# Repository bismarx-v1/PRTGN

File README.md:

# PRTGN
OwO whats this (This repo contains electronics, mechanical and software data for a protogen visor)

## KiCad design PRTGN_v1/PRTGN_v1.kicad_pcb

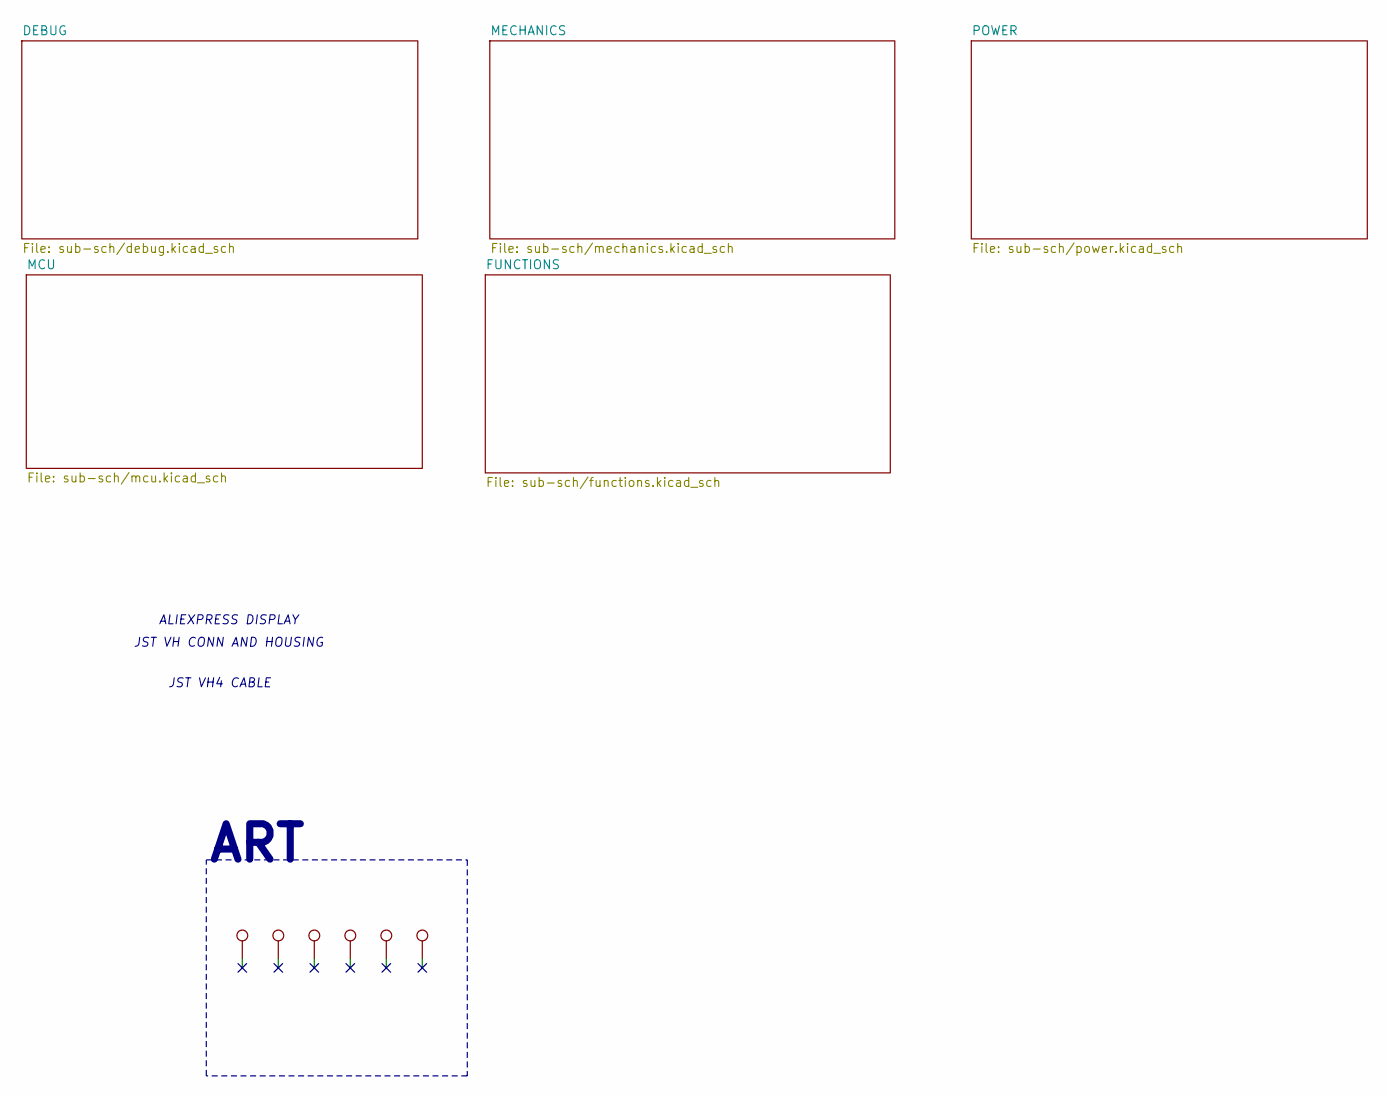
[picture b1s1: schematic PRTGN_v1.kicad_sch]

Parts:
TPd1: TestPoint; APERTURE_ART
TPd2: TestPoint; LEGOSHI_SILK
TPd3: TestPoint; BOYKISSER_IMG
TPd4, TPd6: TestPoint; OWO_IMG
TPd8: TestPoint; PURO_CHANGED_IMG

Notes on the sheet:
JST VH4 CABLE
ALIEXPRESS DISPLAY
ART
JST VH CONN AND HOUSING

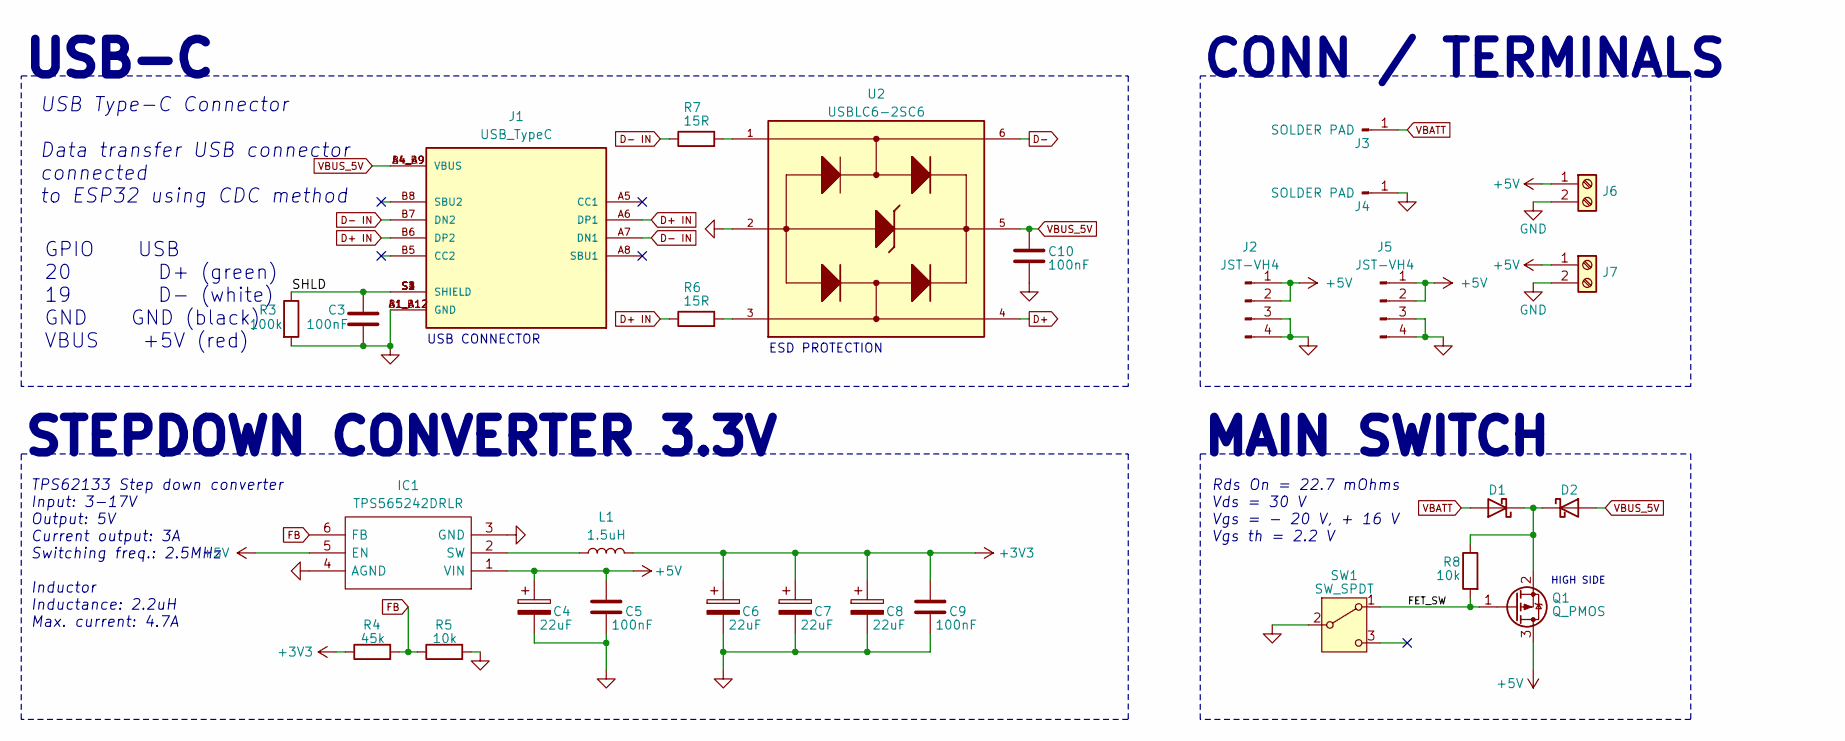
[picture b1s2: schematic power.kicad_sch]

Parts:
C3, C10: 100nF; C_0805_2012Metric
C4, C6, C7, C8: 22uF; CP_EIA-2012-12_Kemet-R
C5, C9: 100nF; C_0805_2012Metric; LCSC C49678
D1, D2: D_Schottky; D_2114_3652Metric
IC1: TPS565242DRLR; SOT-563; Manufacturer_Part_Number TPS565242DRLR; Mouser Part Number 595-TPS565242DRLR
J1: USB_TypeC; HRO_TYPE-C-31-M-12; PARTREV 2020.12.08
J2, J5: JST-VH4; JST_VH_B4P-VH-B_1x04_P3.96mm_Vertical
J3, J4: SOLDER PAD; SolderWirePad_1x01_SMD
J6, J7: Screw_Terminal_01x02; TerminalBlock_Phoenix_MKDS-1,5-2-5.08_1x02_P5.08mm_Horizont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
L1: 1.5uH; L_Vishay_IHLP-1212
Q1: Q_PMOS; SOT-23-3
R3: 100k; R_0805_2012Metric
R4: 45k; R_0805_2012Metric; LCSC C17470
R5: 10k; R_0805_2012Metric; LCSC C17633
R6, R7: 15R; R_0805_2012Metric
R8: 10k; R_0805_2012Metric
SW1: SW_SPDT; Custom_SPDT_2.5_Switch
U2: USBLC6-2SC6; TSOT-23-6

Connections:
+3V3: C6.1, C7.1, C8.1, C9.1, L1.2, R4.1; also elsewhere on the board
+5V: C4.1, C5.1, IC1.1 (VIN), IC1.5 (EN), J2.1, J2.2, J5.1, J5.2, J6.1, J7.1, Q1.3 (D); also elsewhere on the board
/POWER/FET_SW: Q1.1 (G), R8.2, SW1.1 (A)
/POWER/SHLD: C3.2, J1.S1 (SHIELD), J1.S2 (SHIELD), J1.S3 (SHIELD), J1.S4 (SHIELD), R3.1
D+: U2.4; also elsewhere on the board
D+ IN: J1.A6 (DP1), J1.B6 (DP2), R6.1
D-: U2.6; also elsewhere on the board
D- IN: J1.A7 (DN1), J1.B7 (DN2), R7.1
FB: IC1.6 (FB), R4.2, R5.1
GND: C3.1, C4.2, C5.2, C6.2, C7.2, C8.2, C9.2, C10.2, IC1.3 (GND), IC1.4 (AGND), J1.A1_B12 (GND), J1.B1_A12 (GND), J2.3, J2.4, J4.1, J5.3, J5.4, J6.2, J7.2, R3.2, R5.2, SW1.2 (B), U2.2; also elsewhere on the board
unnamed: D1.1 (K), D2.1 (K), Q1.2 (S), R8.1
unnamed: IC1.2 (SW), L1.1
unnamed: R6.2, U2.3
unnamed: R7.2, U2.1
VBATT: D1.2 (A), J3.1; also elsewhere on the board
VBUS_5V: C10.1, D2.2 (A), J1.A4_B9 (VBUS), J1.B4_A9 (VBUS), U2.5; also elsewhere on the board

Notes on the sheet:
Rds On = 22.7 mOhms Vds = 30 V Vgs = - 20 V, + 16 V Vgs th = 2.2 V
USB CONNECTOR
USB-C
USB Type-C Connector Data transfer USB connector connected to ESP32 using CDC method
ESD PROTECTION
MAIN SWITCH
TPS62133 Step down converter Input: 3-17V Output: 5V Current output: 3A Switching freq.: 2.5MHz Inductor Inductance: 2.2uH Max. current: 4.7A
HIGH SIDE
GPIO USB 20 D+ (green) 19 D- (white) GND GND (black) VBUS +5V (red)
STEPDOWN CONVERTER 3.3V
CONN / TERMINALS

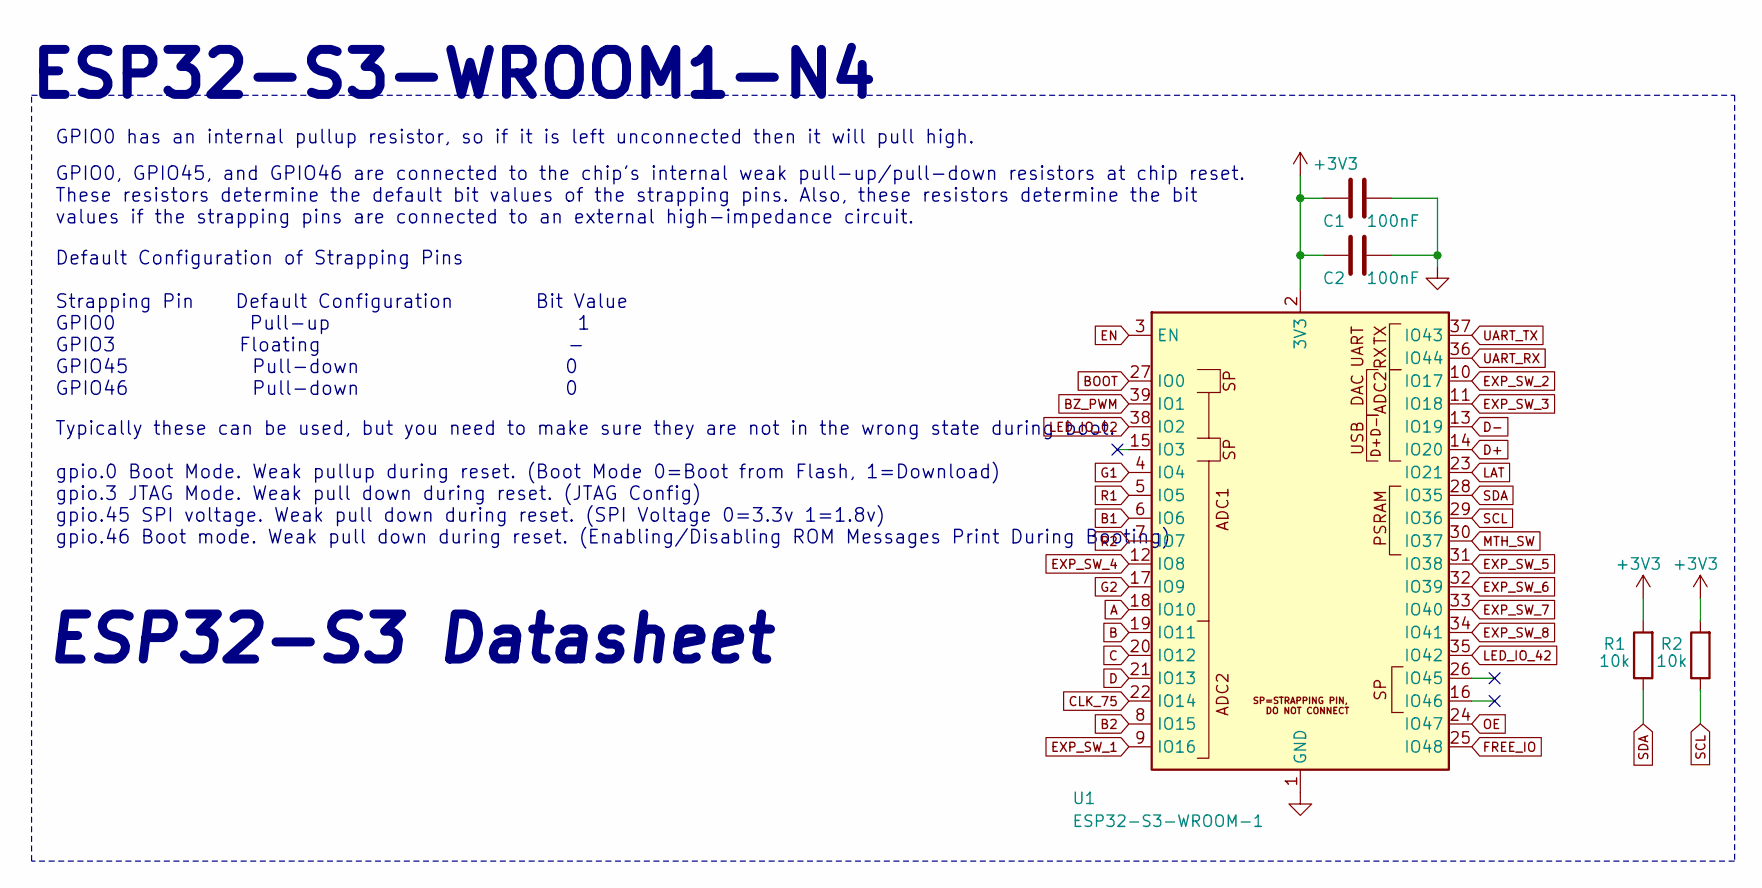
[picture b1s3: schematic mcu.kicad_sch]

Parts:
C1, C2: 100nF; C_0805_2012Metric
R1, R2: 10k; R_0805_2012Metric
U1: ESP32-S3-WROOM-1

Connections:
+3V3: C1.1, C2.1, R1.2, R2.2, U1.2 (3V3); also elsewhere on the board
A: U1.18 (IO10); also elsewhere on the board
B: U1.19 (IO11); also elsewhere on the board
B1: U1.6 (IO6); also elsewhere on the board
B2: U1.8 (IO15); also elsewhere on the board
BOOT: U1.27 (IO0); also elsewhere on the board
BZ_PWM: U1.39 (IO1); also elsewhere on the board
C: U1.20 (IO12); also elsewhere on the board
CLK_75: U1.22 (IO14); also elsewhere on the board
D: U1.21 (IO13); also elsewhere on the board
D+: U1.14 (IO20); also elsewhere on the board
D-: U1.13 (IO19); also elsewhere on the board
EN: U1.3 (EN); also elsewhere on the board
EXP_SW_1: U1.9 (IO16); also elsewhere on the board
EXP_SW_2: U1.10 (IO17); also elsewhere on the board
EXP_SW_3: U1.11 (IO18); also elsewhere on the board
EXP_SW_4: U1.12 (IO8); also elsewhere on the board
EXP_SW_5: U1.31 (IO38); also elsewhere on the board
EXP_SW_6: U1.32 (IO39); also elsewhere on the board
EXP_SW_7: U1.33 (IO40); also elsewhere on the board
EXP_SW_8: U1.34 (IO41); also elsewhere on the board
FREE_IO: U1.25 (IO48); also elsewhere on the board
G1: U1.4 (IO4); also elsewhere on the board
G2: U1.17 (IO9); also elsewhere on the board
GND: C1.2, C2.2, U1.1 (GND), U1.40 (GND), U1.41 (GND); also elsewhere on the board
LAT: U1.23 (IO21); also elsewhere on the board
LED_IO_02: U1.38 (IO2); also elsewhere on the board
LED_IO_42: U1.35 (IO42); also elsewhere on the board
MTH_SW: U1.30 (IO37); also elsewhere on the board
OE: U1.24 (IO47); also elsewhere on the board
R1: U1.5 (IO5); also elsewhere on the board
R2: U1.7 (IO7); also elsewhere on the board
SCL: R2.1, U1.29 (IO36); also elsewhere on the board
SDA: R1.1, U1.28 (IO35); also elsewhere on the board
UART_RX: U1.36 (IO44); also elsewhere on the board
UART_TX: U1.37 (IO43); also elsewhere on the board

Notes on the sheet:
GPIO0, GPIO45, and GPIO46 are connected to the chip's internal weak pull-up/pull-down resistors at chip reset. These resistors determine the default bit values of the strapping pins. Also, these resistors determine the bit values if the strapping pins are connected to an external high-impedance cir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
Default Configuration of Strapping Pins Strapping Pin Default Configuration Bit Value GPIO0 Pull-up 1 GPIO3 Floating - GPIO45 Pull-down 0 GPIO46 Pull-down 0
ESP32-S3 Datasheet
GPIO0 has an internal pullup resistor, so if it is left unconnected then it will pull high.
Typically these can be used, but you need to make sure they are not in the wrong state during boot. gpio.0 Boot Mode. Weak pullup during reset. (Boot Mode 0=Boot from Flash, 1=Download) gpio.3 JTAG Mode. Weak pull down during reset. (JTAG Config) gpio.45 SPI voltage. Weak pull down during reset. (S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
ESP32-S3-WROOM1-N4

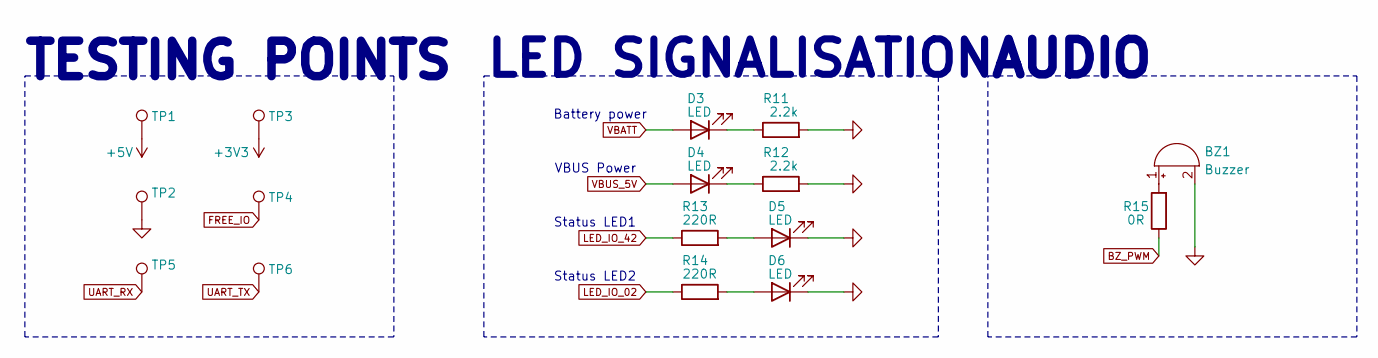
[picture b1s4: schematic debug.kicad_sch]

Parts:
BZ1: Buzzer; AST0827MW-03BTRQ_MAL
D3, D4, D5, D6: LED; LED_0805_2012Metric
R11, R12: 2.2k; R_0805_2012Metric
R13, R14: 220R; R_0805_2012Metric
R15: 0R; R_0805_2012Metric; LCSC C17633
TP1, TP2, TP3, TP4, TP5, TP6: TestPoint; TestPoint_Pad_D1.0mm

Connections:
+3V3: TP3.1; also elsewhere on the board
+5V: TP1.1; also elsewhere on the board
BZ_PWM: R15.1; also elsewhere on the board
FREE_IO: TP4.1; also elsewhere on the board
GND: BZ1.2 (-), D5.1 (K), D6.1 (K), R11.2, R12.2, TP2.1; also elsewhere on the board
LED_IO_02: R14.1; also elsewhere on the board
LED_IO_42: R13.1; also elsewhere on the board
unnamed: BZ1.1 (+), R15.2
unnamed: D3.1 (K), R11.1
unnamed: D4.1 (K), R12.1
unnamed: D5.2 (A), R13.2
unnamed: D6.2 (A), R14.2
UART_RX: TP5.1; also elsewhere on the board
UART_TX: TP6.1; also elsewhere on the board
VBATT: D3.2 (A); also elsewhere on the board
VBUS_5V: D4.2 (A); also elsewhere on the board

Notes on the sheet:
Battery power
Status LED1
AUDIO
TESTING POINTS
Status LED2
LED SIGNALISATION
VBUS Power

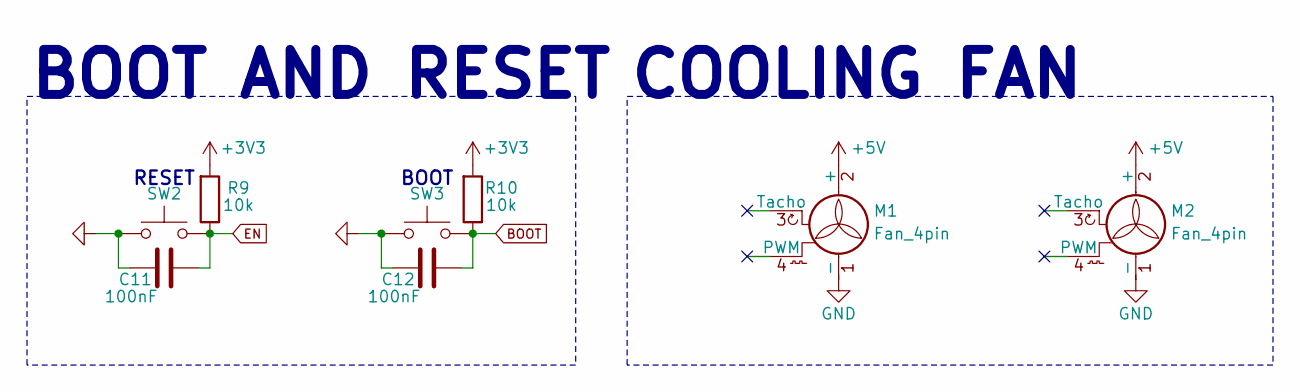
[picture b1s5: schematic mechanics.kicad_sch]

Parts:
C11, C12: 100nF; C_0805_2012Metric
M1, M2: Fan_4pin; FanPinHeader_1x04_P2.54mm_Vertical
R9, R10: 10k; R_0805_2012Metric
SW2, SW3: SW_Push; SW_SPST_EVQPE1

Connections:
+3V3: R9.2, R10.2; also elsewhere on the board
+5V: M1.2 (+), M2.2 (+); also elsewhere on the board
BOOT: C12.2, R10.1, SW3.2; also elsewhere on the board
EN: C11.2, R9.1, SW2.2; also elsewhere on the board
GND: C11.1, C12.1, M1.1 (-), M2.1 (-), SW2.1, SW3.1; also elsewhere on the board

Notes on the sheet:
COOLING FAN
BOOT AND RESET
RESET
BOOT

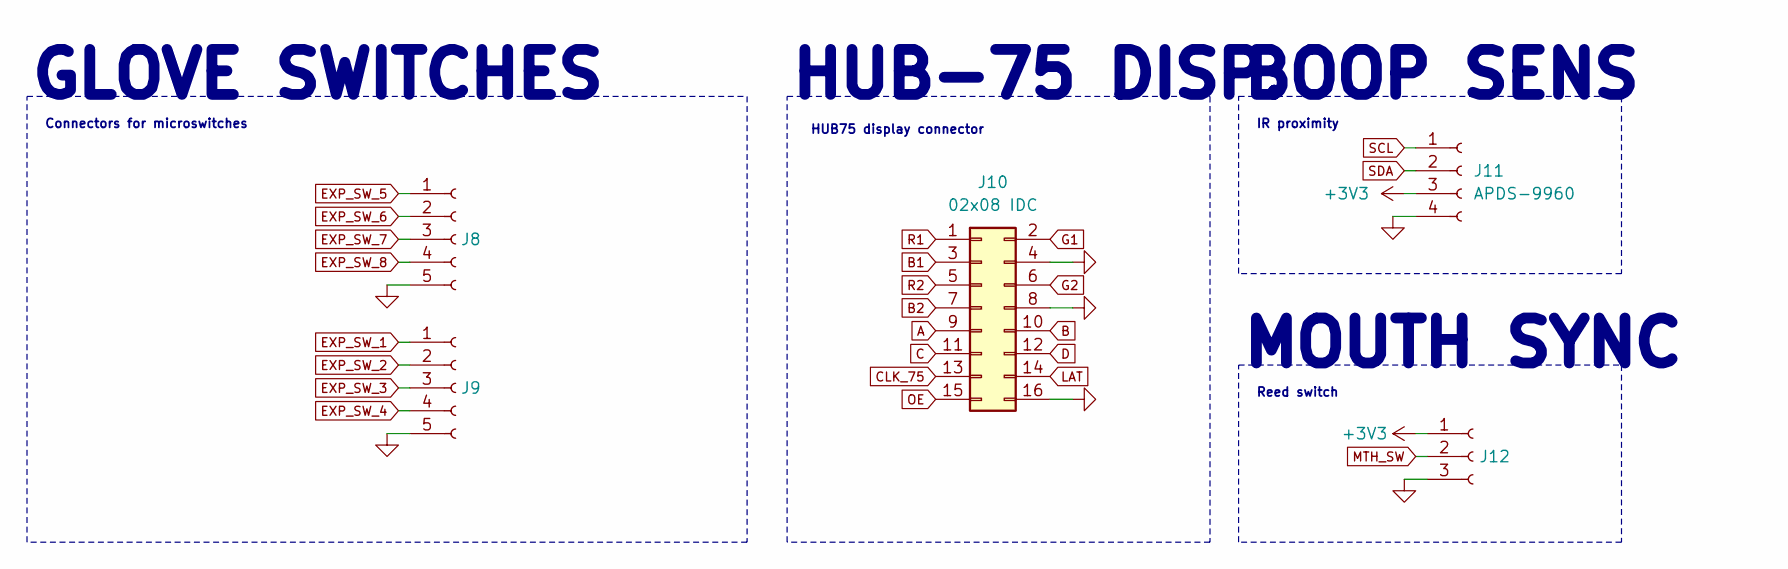
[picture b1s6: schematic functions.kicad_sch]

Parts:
J8, J9: Conn_01x05_Socket; SolderWire-Relief-5pin
J10: 02x08 IDC; IDC-Header_2x08_P2.54mm_Vertical_SMD
J11: APDS-9960; SolderWire-Relief-4pin
J12: Conn_01x03_Socket; SolderWire-Relief-3pin

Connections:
+3V3: J11.3, J12.1; also elsewhere on the board
A: J10.9; also elsewhere on the board
B: J10.10; also elsewhere on the board
B1: J10.3; also elsewhere on the board
B2: J10.7; also elsewhere on the board
C: J10.11; also elsewhere on the board
CLK_75: J10.13; also elsewhere on the board
D: J10.12; also elsewhere on the board
EXP_SW_1: J9.1; also elsewhere on the board
EXP_SW_2: J9.2; also elsewhere on the board
EXP_SW_3: J9.3; also elsewhere on the board
EXP_SW_4: J9.4; also elsewhere on the board
EXP_SW_5: J8.1; also elsewhere on the board
EXP_SW_6: J8.2; also elsewhere on the board
EXP_SW_7: J8.3; also elsewhere on the board
EXP_SW_8: J8.4; also elsewhere on the board
G1: J10.2; also elsewhere on the board
G2: J10.6; also elsewhere on the board
GND: J8.5, J9.5, J10.4, J10.8, J10.16, J11.4, J12.3; also elsewhere on the board
LAT: J10.14; also elsewhere on the board
MTH_SW: J12.2; also elsewhere on the board
OE: J10.15; also elsewhere on the board
R1: J10.1; also elsewhere on the board
R2: J10.5; also elsewhere on the board
SCL: J11.1; also elsewhere on the board
SDA: J11.2; also elsewhere on the board

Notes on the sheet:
BOOP SENS
IR proximity
GLOVE SWITCHES
HUB75 display connector
HUB-75 DISP.
MOUTH SYNC
Reed switch
Connectors for microswitches

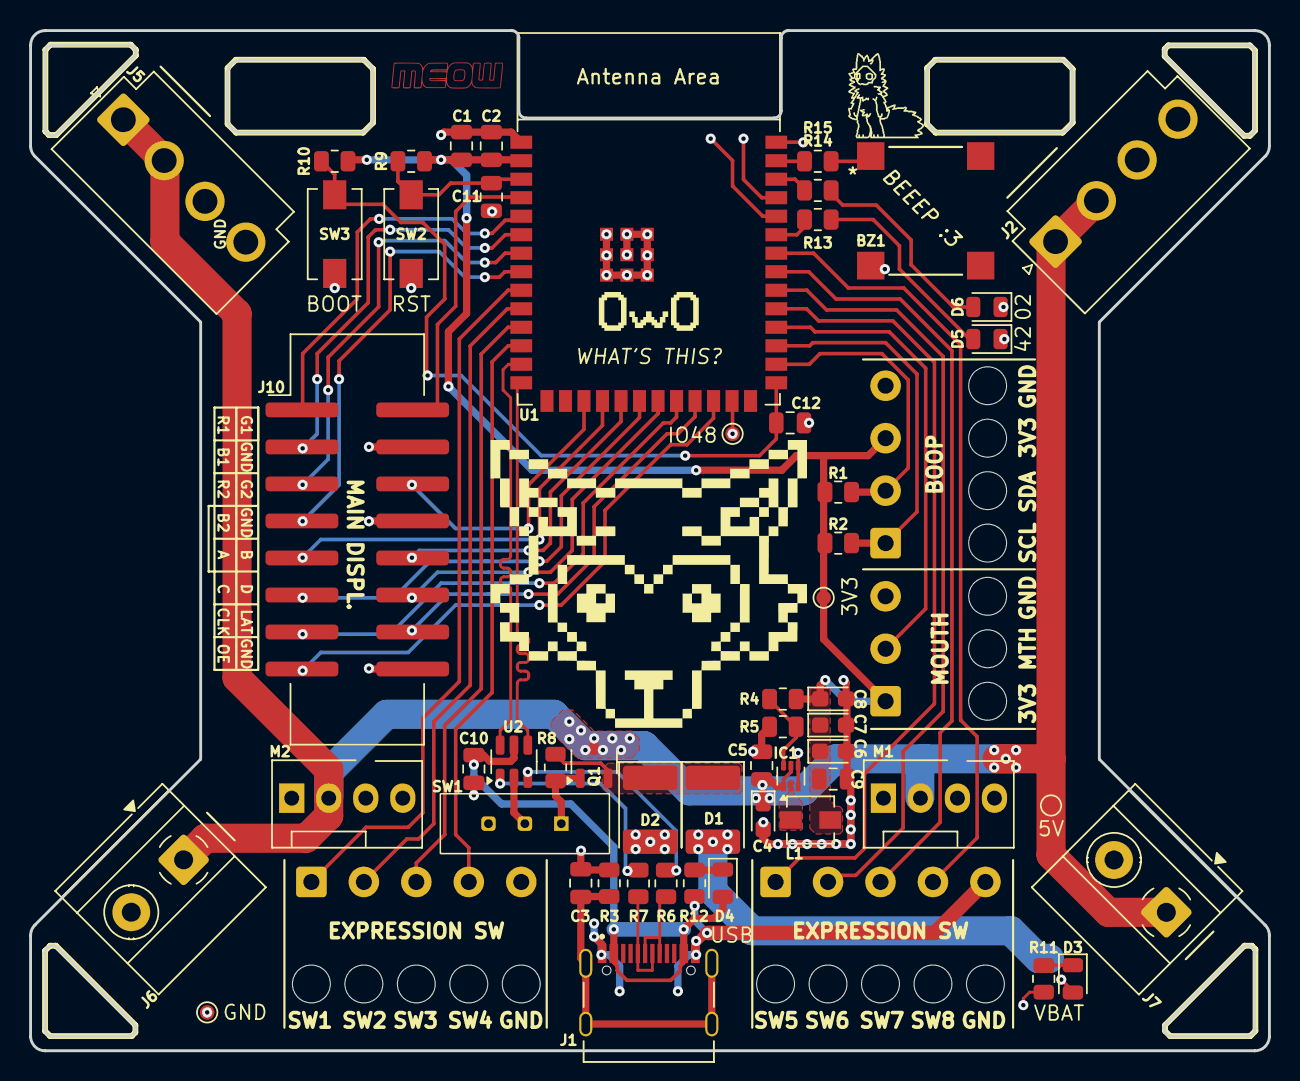
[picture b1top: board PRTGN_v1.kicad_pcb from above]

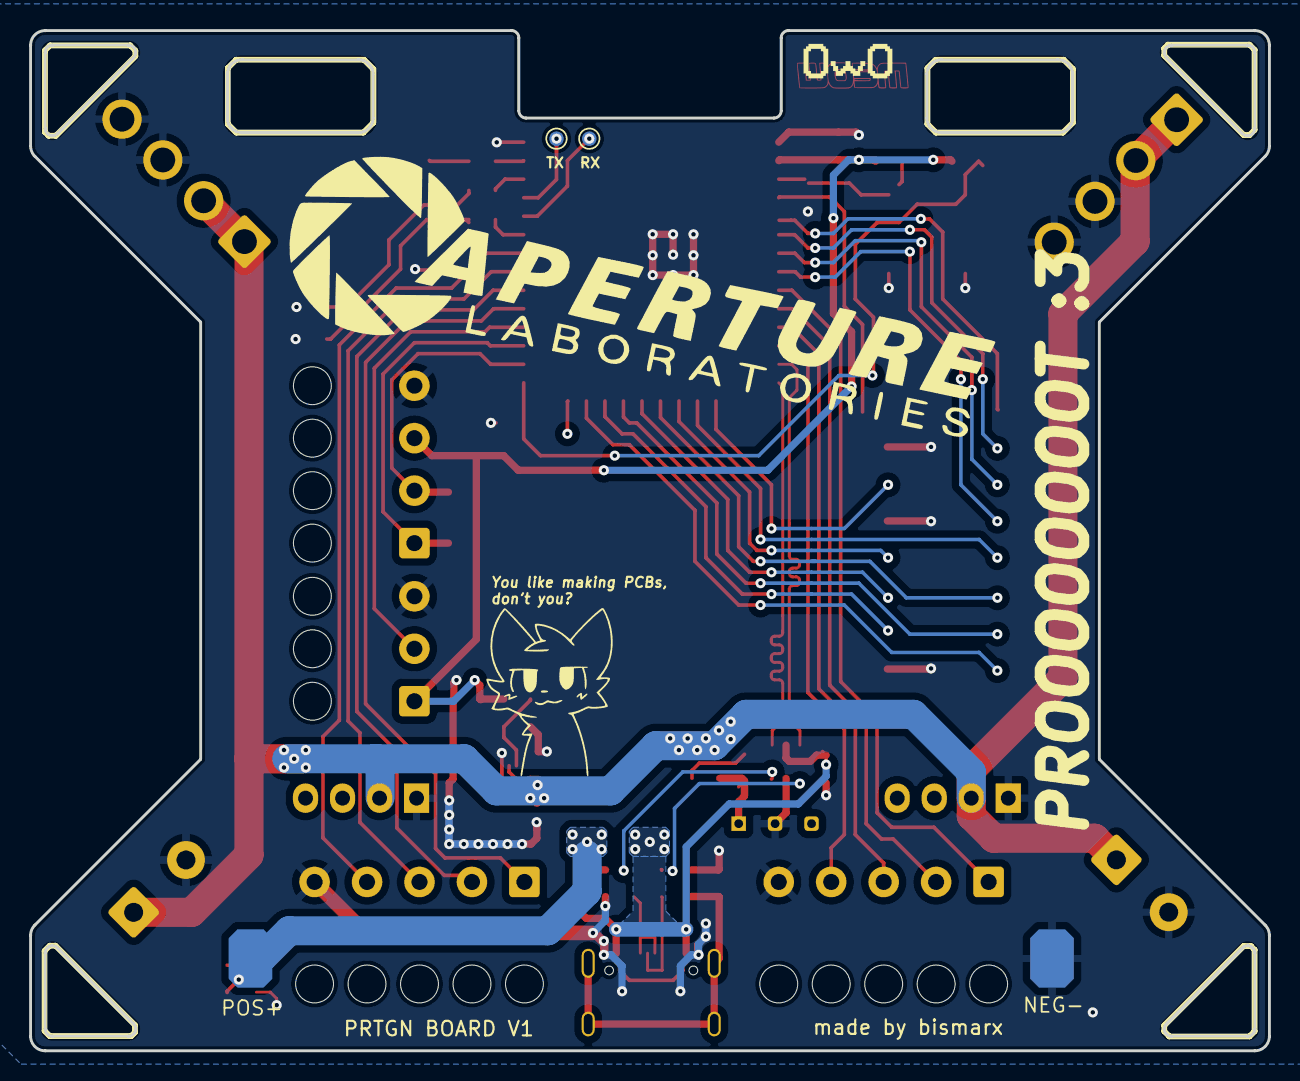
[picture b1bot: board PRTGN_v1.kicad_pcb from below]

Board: 2 copper layers, 85.0 x 70.0 mm, 68 parts (7 on the bottom side), 53 nets.

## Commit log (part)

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2025-06-13 first push (kicad)
2025-06-14 should add gitignore
2025-07-03 uppdates
2025-07-03 pcb update
2025-07-04 routing
2025-07-23 pcb updates
2025-08-03 PCV updates
2025-08-04 pcb layout.
2025-08-05 layout PCB etc
2025-08-09 pcb silksdnree neded
2025-08-10 final
2025-08-10 prtgnd
2025-08-10 didnt close it
2025-08-12 prtoogen visdor silkscreenm - order
2025-09-05 no changes
2026-06-01 New ESP config added
2026-06-07 new code
